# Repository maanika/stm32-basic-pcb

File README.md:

# STM32 PCB Design Project

## Overview

This repository contains the design files for a custom PCB based on the STM32 microcontroller.
The PCB is designed for prototyping and development, exposing key interfaces including UART, I2C, and SWD.

## Features

STM32 Microcontroller (STM32F103C8T6): Central processing unit for the board.

Exposed Interfaces:

UART: For serial communication.

I2C: For connecting peripherals like sensors or displays.

SWD: For debugging and programming.

USB: For data transfer and power.

## Project Structure

`/production`: Fabrication toolkit output. Contains the gerber (stm32_basic.zip), bom, and position files for manufacturing.

`/stm32_basic.kicad_pro`: Project file that defines the KiCad project.

`/stm32_basic.kicad_sch`: Circuit schematic.

`/stm32_basic.kicad_pcb`: Circuit layout.

`/parts`: Includes 3D models for pcb parts.

`/docs`: Images.

TO-D0

`/firmware`: Sample firmware for testing the exposed interfaces.

## PCB

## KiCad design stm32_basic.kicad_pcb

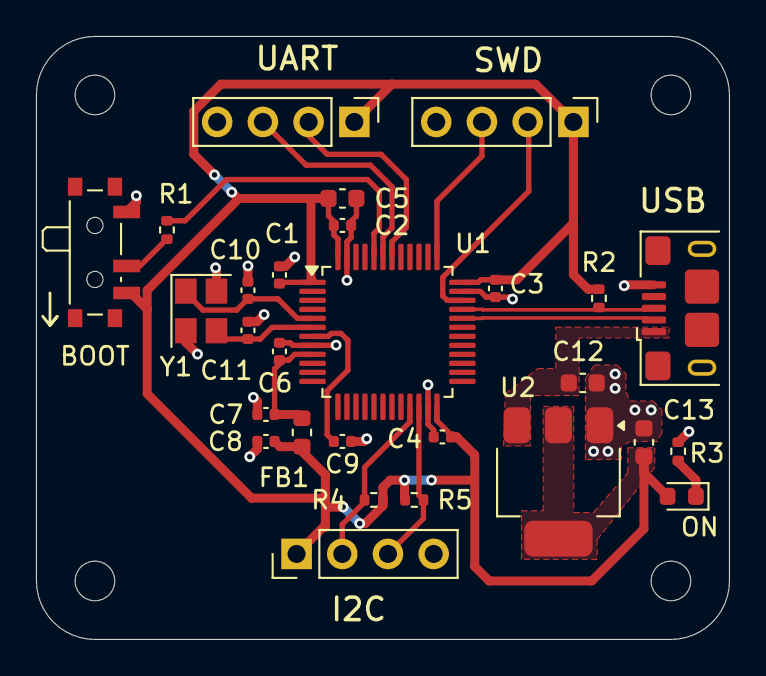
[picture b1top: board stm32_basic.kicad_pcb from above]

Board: 2 copper layers, 38.5 x 33.5 mm, 32 parts (0 on the bottom side), 18 nets.

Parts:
BOOT: SW_SPDT; SW_SPDT_PCM12
C1, C2, C3, C4, C9: 100n; C_0402_1005Metric
C5, C12, C13: 10u; C_0603_1608Metric
C6: 10n; C_0402_1005Metric
C7, C8: 1u; C_0402_1005Metric
C10, C11: 10p; C_0402_1005Metric
DEBUG: Conn_01x04_Pin; PinHeader_1x04_P2.54mm_Vertical
FB1: 120R; L_0603_1608Metric
H1, H2, H3, H4: MountingHole; MountingHole_2.2mm_M2
I2C: Conn_01x04_Pin; PinHeader_1x04_P2.54mm_Vertical
J1: USB_B_Micro; USB_Micro-B_Amphenol_10118193-0001LF_Horizontal
ON: GREEN; LED_0603_1608Metric
R1: 10k; R_0402_1005Metric
R2, R3: 1k5; R_0402_1005Metric
R4, R5: 2k2; R_0402_1005Metric
U1: STM32F103C8T6; LQFP-48_7x7mm_P0.5mm
U2: AMS1117-3.3; SOT-223-3_TabPin2
UART: Conn_01x04_Pin; PinHeader_1x04_P2.54mm_Vertical
Y1: 16MHz; Crystal_SMD_3225-4Pin_3.2x2.5mm

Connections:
+3.3V: BOOT.3 (C), C1.1, C2.1, C3.1, C4.1, C5.1, C8.1, C13.1, DEBUG.1, FB1.2, I2C.1, ON.2 (A), R2.1, R4.1, R5.1, U1.1 (VBAT), U1.24 (VDD), U1.36 (VDD), U1.48 (VDD), U2.2 (VO), UART.1
+3.3VA: C6.1, C7.1, FB1.1, U1.9 (VDDA)
/BOOT0: R1.2, U1.44 (BOOT0)
/HSE_IN: C10.1, U1.5 (PD0), Y1.1
/HSE_OUT: C11.1, U1.6 (PD1), Y1.3
/I2C_SCL: I2C.2, R4.2, U1.21 (PB10)
/I2C_SDA: I2C.3, R5.2, U1.22 (PB11)
/NRST: C9.2, U1.7 (NRST)
/PWR_LED_K: ON.1 (K), R3.1
/SWCLK: DEBUG.3, U1.37 (PA14)
/SWDIO: DEBUG.2, U1.34 (PA13)
/SW_BOOT0: BOOT.2 (B), R1.1
/USART1_RX: U1.43 (PB7), UART.3
/USART1_TX: U1.42 (PB6), UART.2
/USB_D+: J1.3 (D+), R2.2, U1.33 (PA12)
/USB_D-: J1.2 (D-), U1.32 (PA11)
GND: BOOT.1 (A), C1.2, C2.2, C3.2, C4.2, C5.2, C6.2, C7.2, C8.2, C9.1, C10.2, C11.2, C12.2, C13.2, DEBUG.4, I2C.4, J1.5 (GND), R3.2, U1.8 (VSSA), U1.23 (VSS), U1.35 (VSS), U1.47 (VSS), U2.1 (GND), UART.4, Y1.2, Y1.4
VBUS: C12.1, J1.1 (VBUS), U2.3 (VI)

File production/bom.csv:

Designator,Footprint,Quantity,Value,LCSC Part #
BOOT,SW_SPDT_PCM12,1,SW_SPDT,
"C1, C2, C3, C4, C9",0402,5,100n,
"C10, C11",0402,2,10p,
"C12, C13, C5",0603,3,10u,
C6,0402,1,10n,
"C7, C8",0402,2,1u,
"DEBUG, I2C, UART",PinHeader_1x04_P2.54mm_Vertical,3,Conn_01x04_Pin,
FB1,0603,1,120R,
J1,USB_Micro-B_Amphenol_10118193-0001LF_Horizontal,1,USB_B_Micro,
ON,0603,1,GREEN,
R1,0402,1,10k,
"R2, R3",0402,2,1k5,
"R4, R5",0402,2,2k2,
U1,LQFP-48_7x7mm_P0.5mm,1,STM32F103C8T6,
U2,SOT-223-3_TabPin2,1,AMS1117-3.3,
Y1,Crystal_SMD_3225-4Pin_3.2x2.5mm,1,16MHz,

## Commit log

2024-12-14 Adding project files
    - production files for jlpcb
    - kicad files: sch, pro, and pcb
